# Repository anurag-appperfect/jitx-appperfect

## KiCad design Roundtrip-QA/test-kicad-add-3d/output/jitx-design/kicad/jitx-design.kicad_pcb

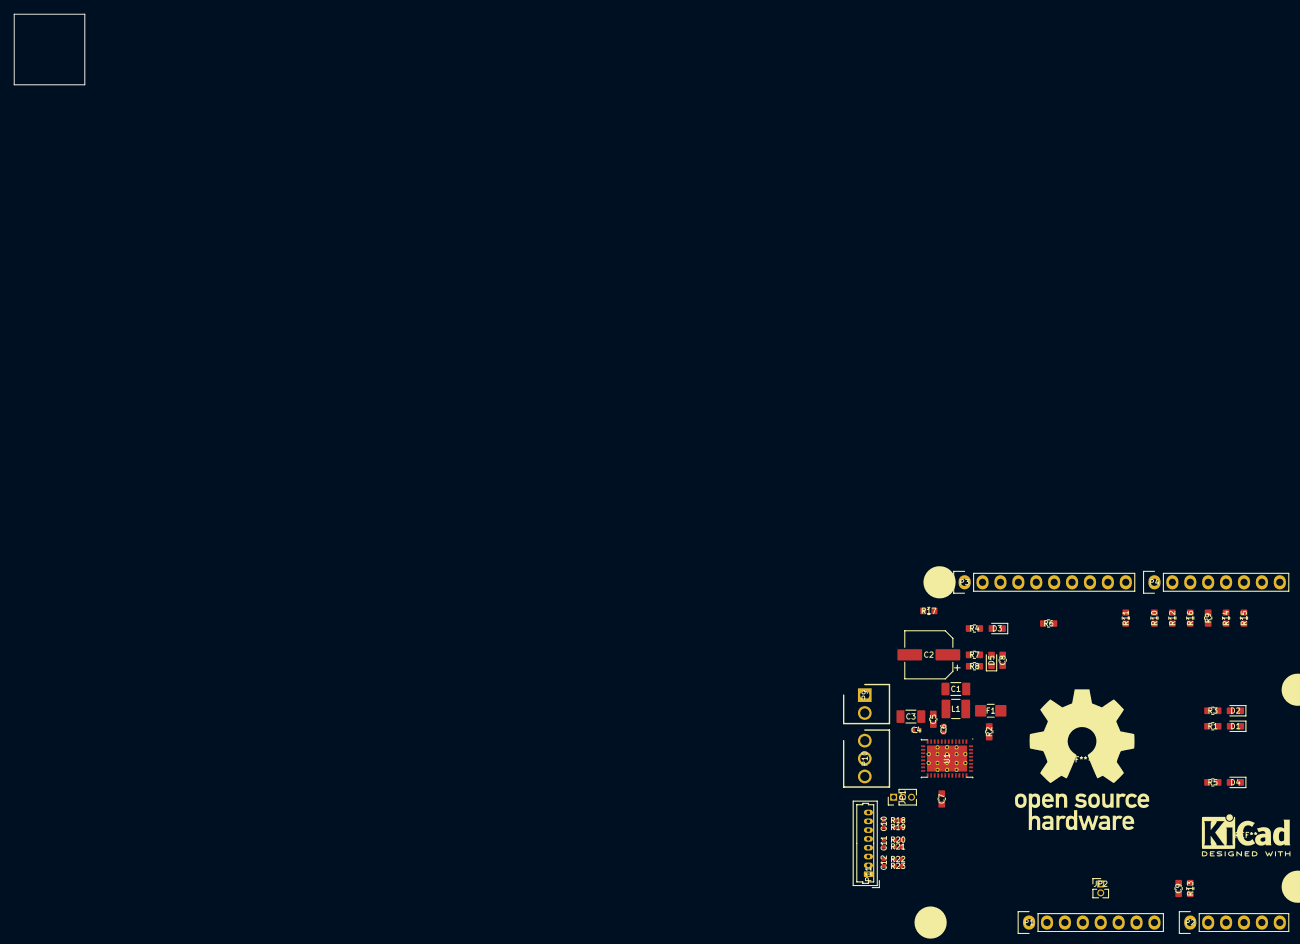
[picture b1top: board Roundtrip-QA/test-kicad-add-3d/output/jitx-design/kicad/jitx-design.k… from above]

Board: 4 copper layers, 57 parts (0 on the bottom side), 47 nets, no tracks yet.

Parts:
C1: c_1206_3216metric
C2: cp_elec_63x77
C3: c_1206_3216metric_1
C4, C6, C10, C11, C12: c_0402_1005metric
C5, C7, C8, C9: c_0603_1608metric
D1, D2, D3, D4: led_0603_1608metric
D5: d_0603_1608metric
F1: fuse_1206_3216metric_castellated
JP1: pinheader_1x03_p127mm_vertical
JP2: pinheader_1x02_p127mm_vertical
L1: l_1210_3225metric
P1: socket_strip_arduino_1x08
P2: socket_strip_arduino_1x06locked
P3: socket_strip_arduino_1x10locked
P4: socket_strip_arduino_1x08locked
P5, P6, P7, P8: arduino_1pinlocked
P9: Pkg_39773_0002
P10: Pkg_39773_0003
P11: molex_picoblade_53047_0810_1x08_p125mm_vertical
R1, R2, R3, R4, R5, R6, R7, R8, R9, R10, R11, R12, R13, R14, R15, R16, R17: r_0603_1608metric
R18, R19, R20, R21, R22, R23: r_0402_1005metric
SW1: kailh_pcb_socket_1u_cutout_pkg
U1: qfn_40_ep_5x7_pitch05mm

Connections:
A0: P2.1, R13.2
A1: C8.2, D5.2, P2.2, R7.1, R8.1
A4SDA: P2.5, P3.2
A5SCL: P2.6, P3.1
BRAKE: R10.2, U1.38
CS: R9.2, U1.36
DRVOFF: R16.2, U1.21
FAULT: D4.1, R15.2, U1.22
FB: C1.2, F1.2, L1.1, U1.3
FGOUT: R2.2, R12.2, U1.40
GND: C1.1, C7.2, C8.1, C9.1, D1.1, D2.1, D3.1, D5.1, P1.6, P1.7, P3.4, P11.1, R8.2, R17.2, R19.2, R21.2, R23.2, U1.2, U1.4, U1.41, U1.42, U1.43, U1.44, U1.45, U1.46, U1.47, U1.48, U1.49, U1.50, U1.51, U1.52, U1.53, U1.54, U1.55, U1.56, U1.57
GNDPWR: C2.2, C3.1, C4.1, P9.2, R17.1, U1.12, U1.15, U1.18
HAN: C10.1, P11.6, R19.1, U1.28
HAP: C10.2, P11.7, R18.1, U1.27
HBN: C11.1, P11.4, R21.1, U1.30
HBP: C11.2, P11.5, R20.1, U1.29
HCN: C12.1, P11.2, R23.1, U1.32
HCP: C12.2, P11.3, R22.1, U1.31
ILIM: C9.2, R13.1, U1.37
Net-C5-Pad1: C5.1, U1.8
Net-C6-Pad1: C6.1, U1.7
Net-C6-Pad2: C6.2, U1.6
Net-D1-Pad2: D1.2, R1.2
Net-D2-Pad2: D2.2, R3.2
Net-D3-Pad2: D3.2, R4.2
Net-D4-Pad2: D4.2, R5.2
Net-JP1-Pad2: JP1.2, P11.8
PWM: R11.2, U1.39
SLEEP: R14.2, U1.23
SW: L1.2, U1.5
U: P10.1, U1.13, U1.14
V: P10.2, U1.16, U1.17
VCC: F1.1, JP1.3, JP2.1, R3.1
W: P10.3, U1.19, U1.20
p2: P4.6, R15.1
p3**: P4.5, R14.1
p4: P4.4, R9.1
p5**: P4.3, R16.1
p6**: P4.2, R12.1
p7: P4.1, R10.1
p8: P3.10, R11.1
p11**MOSI: P3.7, U1.34
p12MISO: P3.6, R6.2, U1.33
p13SCK: P3.5, U1.35
p+3-3V: C7.1, JP1.1, P1.4, R1.1, R2.1, R5.1, R6.1, R18.2, R20.2, R22.2, U1.25
p+5V: JP2.2, P1.5
p+36V: C2.1, C3.2, C4.2, C5.2, P9.1, R4.1, R7.2, U1.9, U1.10, U1.11

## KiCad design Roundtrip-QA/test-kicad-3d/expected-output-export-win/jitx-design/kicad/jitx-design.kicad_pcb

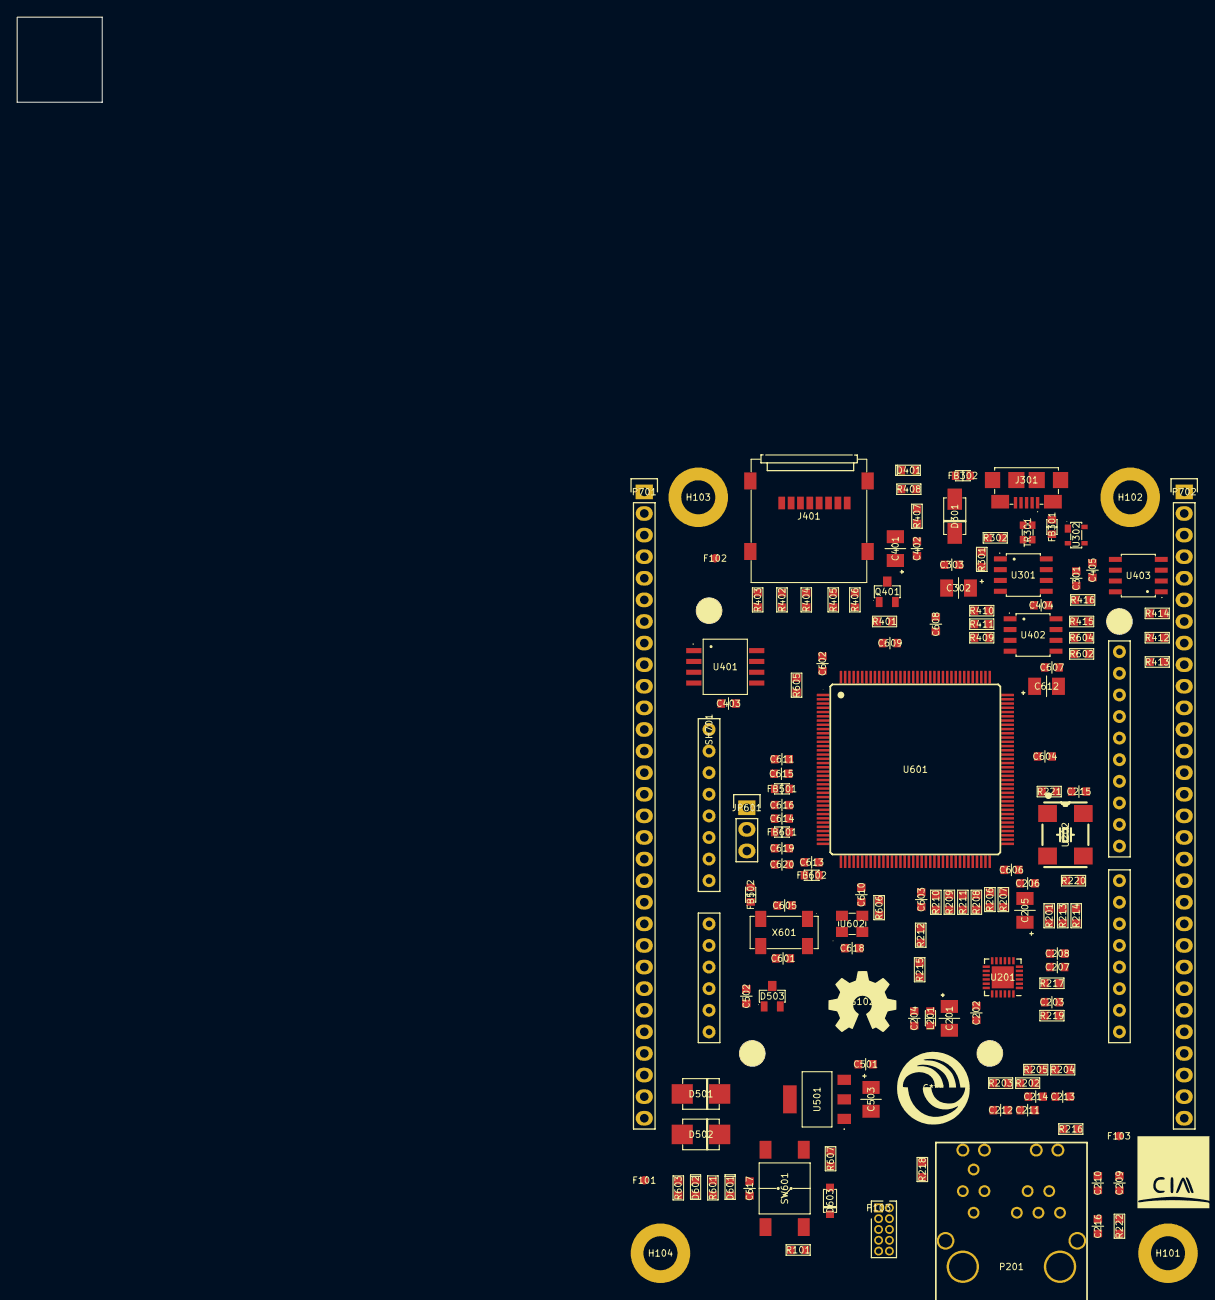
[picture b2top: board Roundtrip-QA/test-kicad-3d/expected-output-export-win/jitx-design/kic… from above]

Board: 4 copper layers, 141 parts (0 on the bottom side), 169 nets, no tracks yet.

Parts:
C201, C205: c_1206pol_1
C202, C203, C204, C206, C207, C208, C209, C210, C211, C212, C213, C214, C215: c_0603
C216, C301, C303, C402, C403, C404, C405, C501, C502, C601, C602, C603, C604, C605, C606, C607, C608, C609, C610, C611, C613, C614, C615, C616, C617, C618, C619, C620: c_0603_1
C302, C503, C612: c_1206pol_lp
C401: c_1206pol
D301: do_214ac_sma
D401, D601, D602: led_0603
D501, D502: do_214aa_smb
D503: sot_23
D603: sod_123
F101, F102, F103: fiducial_1mm_lp
FB301, FB302, FB501, FB502, FB601, FB602: fb_0603
G101: logo_ciaa_lp
G102: oshwa_lp
H101, H102, H103, H104: pcb_hole_lp
J301: usb_microab
J401: microsd_hinged
JP601: pin_header_straight_1x03
L201: fb_0603_1
P103: pin_header_straight_2x05_pitch127mm
P201: rj45_si_52003_f_poe_eth
P701, P702: pin_header_straight_1x30
Q401: sot_23_lp
R101, R222, R301, R302, R401, R402, R403, R404, R405, R406, R407, R408, R409, R410, R411, R412, R413, R414, R415, R416, R601, R602, R603, R604, R605, R606, R607: r_0603
R201, R202, R203, R204, R205, R206, R207, R208, R209, R210, R211, R212, R213, R214, R215, R216, R217, R218, R219, R220, R221: r_0603_1
SH701: arduino_as_uno_r3locked
SW601: tact_smd_4
TR301: srf2012
U201: qfn_24_1ep_4x4mm_pitch05mm
U202: oscillator_70x50mm
U301: soic_8
U302: sot_143_4
U401: soic_8_wide
U402, U403: soic_8_lp
U501: sot_223
U601: lqfp144
U602: si501_c
X601: Pkg_4soj

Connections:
BATPIN: D503.1, P701.20
CPUAIN0: P702.25, U601.77
CPUAIN1: P702.24, U601.78
CPUAIN2: P702.23, U601.79
CPUAIN3: P702.22, U601.80
CPUAUX-UART-CTSSPI-CLK: P701.12, U601.128
CPUAUX-UART-RTSSPI-CS: P701.13, U601.127
CPUAUX-UART-RXSPI-MISO: P701.10, U601.130
CPUAUX-UART-TXSPI-MOSIFTM3-CH2: P701.11, U601.129
CPUCAN-RD: P702.10, U601.98
CPUCAN-TD: P702.9, U601.97
CPUDAC-OUT: P701.18, U601.38
CPUDIN0: P702.13, U601.9
CPUDIN1: P702.14, U601.10
CPUDIN2: P701.23, U601.13
CPUDIN3: P701.24, U601.14
CPUDOUT0: P702.12, U601.95
CPUDOUT1: P702.21, U601.87
CPUDOUT2: P702.20, U601.88
CPUDOUT3: P702.11, U601.96
CPUDOUT4: P701.26, U601.120
CPUDOUT5: P701.27, U601.119
CPUDOUT6: P701.28, U601.118
CPUDOUT7: P701.29, U601.117
CPUEC-AI0: SH701.A0, U601.35
CPUEC-AI1: SH701.A1, U601.36
CPUEC-AI2: SH701.A2, U601.39
CPUEC-AI3: SH701.A3, U601.46
CPUEC-GPIO0: SH701.8, U601.76
CPUEC-GPIO1: SH701.7, U601.75
CPUEC-GPIO2: SH701.4, U601.85
CPUEC-I2C-SCL: SH701.A5-1, SH701.A5-2, U601.83
CPUEC-I2C-SDA: SH701.A4-1, SH701.A4-2, U601.84
CPUEC-PWM0: SH701.6, U601.60
CPUEC-PWM1: SH701.5, U601.61
CPUEC-PWM2: SH701.3, U601.62
CPUEC-PWM3: SH701.2, U601.63
CPUEC-PWM4: SH701.10, U601.54
CPUEC-PWM5: SH701.9, U601.15
CPUETH-CRS-DV: R211.1, U601.66
CPUETH-MDC: R214.1, U601.82
CPUETH-MDIO: R213.1, U601.81
CPUETH-REF-CLK: R220.2, U201.5, U601.72
CPUETH-RST: U201.15, U601.73
CPUETH-RXD0: R209.1, U601.65
CPUETH-RXD1: R210.1, U601.64
CPUETH-RXER: R212.2, U601.55
CPUETH-TXD0: R206.1, U601.68
CPUETH-TXD1: R207.1, U601.69
CPUETH-TXEN: R208.1, U601.67
CPUGPIO0: P701.9, U601.116
CPUGPIO1: P702.2, U601.99
CPUGPIO2: P701.8, U601.115
CPUGPIO3SPI2-SCK: SH701.13, U601.100
CPUGPIO4: P701.2, U601.114
CPUGPIO5SPI2-SOUT: SH701.11, U601.101
CPUGPIO6: P701.3, U601.113
CPUGPIO7SPI2-SIN: SH701.12, U601.102
CPUGPIO8: P701.4, U601.112
CPUGPIO9: P702.8, U601.103
CPUGPIO10: P702.4, U601.111
CPUGPIO11: P702.7, U601.104
CPUGPIO12: P702.5, U601.110
CPUGPIO13: P702.6, U601.105
CPUGPIO14: P702.3, U601.109
CPUGPIO15: P701.14, U601.106
CPUI2C-SCL: R604.2, U402.6, U403.6, U601.137
CPUI2C-SDA: R602.2, U402.5, U403.5, U601.138
CPUPGA1-DM: P701.22, U601.30
CPUPGA1-DP: P701.21, U601.29
CPUPTB5: P702.15, U601.86
CPURS232-CTS: P702.18, U601.90
CPURS232-RTS: P702.19, U601.89
CPURS232-RXD: P702.17, U601.91
CPURS232-TXD: P702.16, U601.92
CPURS485-DIR: P701.5, U601.131
CPURS485-RXD: P701.6, U601.133
CPURS485-TXD: P701.7, U601.136
CPUSD-CLK: J401.5, R605.2
CPUSD-CMD: J401.3, R404.2, U601.4
CPUSD-DAT0: J401.7, R405.2, U601.2
CPUSD-DAT1: J401.8, R406.2, U601.1
CPUSD-DAT2: J401.1, R403.2, U601.8
CPUSD-DAT3: J401.2, R402.1, U601.7
CPUSD-POW: Q401.1, R401.2, U601.126
CPUSPIFI-CLK: U401.6, U601.141
CPUSPIFI-CS: U401.1, U601.140
CPUSPIFI-HOLD: U401.7, U601.144
CPUSPIFI-MISO: U401.2, U601.143
CPUSPIFI-MOSI: U401.5, U601.142
CPUSPIFI-WP: U401.3, U601.139
CPUUSB-ID: D301.2, J301.4, U601.123
CPUUSBD-N: TR301.3, U302.2, U601.20
CPUUSBD-P: TR301.2, U302.3, U601.19
CPUVREFL: C613.2, C614.2, C616.1, FB602.1, U601.33
EthernetLED-100M: P201.15, R217.2, U201.2
EthernetLED-LINK: P201.12, U201.3
EthernetRX-N: C214.1, P201.5, R205.2, U201.22
EthernetRX-P: C213.1, P201.4, R204.2, U201.23
EthernetTX-N: C212.1, P201.3, R203.2, U201.20
EthernetTX-P: C211.1, P201.1, R202.2, U201.21
GND: C201.2, C202.2, C203.2, C204.2, C205.2, C206.2, C207.2, C208.2, C209.2, C210.2, C211.2, C212.2, C213.2, C214.2, C215.2, C216.2, C301.2, C302.2, C303.2, C401.2, C402.2, C403.2, C404.2, C405.2, C501.2, C502.2, C503.2, C601.2, C602.2, C603.2, C604.2, C605.2, C606.2, C607.2, C608.2, C609.2, C610.2, C611.2, C612.2, C615.2, C617.1, C618.2, D401.2, D601.2, D602.2, FB302.1, FB502.1, J301.5, J401.6, J401.9, J401.10, J401.11, J401.12, P103.3, P103.5, P701.30, P702.1, R218.1, R219.2, R222.2, R301.1, R402.2, R407.2, R410.2, R411.2, R413.2, R414.2, R415.2, R416.2, SH701.GND1, SH701.GND2, SH701.GND3, SW601.2, U201.25, U201.26, U201.27, U201.GND, U202.2, U301.3, U401.4, U402.4, U403.4, U501.1, U601.6, U601.17, U601.18, U601.44, U601.57, U601.71, U601.93, U601.107, U601.121, U601.134, U602.2, X601.2, X601.4
GNDA: C619.2, C620.1, FB502.2, FB602.2, U601.34
GNDPWR: C216.1, H101.1, H102.1, H103.1, H104.1, P201.6, P201.7, P201.16, P201.17, R222.1
IOArefA: C614.1, C616.2, FB601.1, JP601.3, SH701.AREF, U601.32
Net-C207-Pad1: C207.1, C208.1, U201.6
Net-C401-Pad1: C401.1, C402.1, J401.4, Q401.3, R403.1, R404.1, R405.1, R406.1, R407.1, R408.1
Net-C601-Pad1: C601.1, U601.41, X601.3
Net-C605-Pad1: C605.1, U601.40, X601.1
Net-C613-Pad1: C613.1, U601.37
Net-C615-Pad1: C615.1, U601.21
Net-C617-Pad2: C617.2, D603.1, R607.2, SW601.1, U601.74
Net-C619-Pad1: C619.1, C620.2, FB601.2, JP601.2
Net-D401-Pad1: D401.1, R408.2
Net-D601-Pad1: D601.1, R601.1
Net-D602-Pad1: D602.1, R603.1
Net-FB301-Pad2: FB301.2, J301.1
Net-P103-Pad9: P103.9, R101.2
Net-P201-Pad13: P201.13, R218.2
Net-P201-Pad14: P201.14, R216.1
Net-R201-Pad2: R201.2, R213.2, U201.12
Net-R206-Pad2: R206.2, U201.17
Net-R207-Pad2: R207.2, U201.18
Net-R208-Pad2: R208.2, U201.16
Net-R209-Pad2: R209.2, U201.8
Net-R210-Pad2: R210.2, U201.7
Net-R211-Pad2: R211.2, U201.11
Net-R212-Pad1: R212.1, U201.10
Net-R214-Pad2: R214.2, U201.13
Net-R215-Pad2: R215.2, U201.14
Net-R219-Pad1: R219.1, U201.24
Net-R220-Pad1: R220.1, U202.3
Net-R221-Pad1: R221.1, U202.1
Net-R409-Pad1: R409.1, U402.3
Net-R410-Pad1: R410.1, U402.1
Net-R411-Pad1: R411.1, U402.2
Net-R412-Pad2: R412.2, U403.1
Net-R413-Pad1: R413.1, U403.2
Net-R414-Pad1: R414.1, U403.3
Net-R415-Pad1: R415.1, U402.7
Net-R416-Pad1: R416.1, U403.7
Net-R601-Pad2: R601.2, U601.58
Net-R603-Pad2: R603.2, U601.59
Net-R605-Pad1: R605.1, U601.3
Net-R606-Pad1: R606.1, U601.45
Net-R606-Pad2: R606.2, U602.3
PoE-MA-+: P201.8, P702.29
PoE-MA--: P201.9, P702.30
PoE-MB-+: P201.10, P702.27
PoE-MB--: P201.11, P702.28
RESET: D603.2, P103.10, P701.17, SH701.RST
TCK: P103.4, U601.50
TDIEC-UART-RX: P103.8, SH701.0, U601.51
TDOEC-UART-TX: P103.6, SH701.1, U601.52
TMS: P103.2, U601.53
USB-JTAG-UART-RXD: P103.7, P701.16, U601.12
USB-JTAG-UART-TXD: P701.15, R101.1, U601.11
USB-VBUS: C302.1, C303.1, D502.1, FB301.1, U301.6, U301.8, U302.4, U601.22
USBOTGCHS-OTG: D301.1, FB302.2, J301.6, J301.7, J301.8, J301.9, J301.10, J301.11, U302.1
USBOTGUSB0-PPWR: R301.2, U301.1, U601.125
USBOTGUSB0-PWR-FAULT: R302.2, U301.2, U601.124
USBOTGUSB-D-OTG-N: J301.2, TR301.4
USBOTGUSB-D-OTG-P: J301.3, TR301.1
VBAT: C502.1, D503.3, U601.42
VDD-ETH: C201.1, C202.1, C203.1, C209.1, C210.1, L201.2, P201.2, R202.1, R203.1, R204.1, R205.1, R217.1, U201.1, U201.19
p5VPIN: D501.1, P701.19
p+3-3V: C204.1, C205.1, C206.1, C215.1, C403.1, C404.1, C405.1, C503.1, C602.1, C603.1, C604.1, C606.1, C607.1, C608.1, C609.1, C610.1, C611.1, C612.1, C618.1, D503.2, FB501.1, L201.1, P103.1, Q401.2, R201.1, R215.1, R216.2, R221.2, R302.1, R401.1, R409.2, R412.1, R602.1, R604.1, R607.1, SH701.IREF, SH701.p3V3, U201.9, U202.4, U401.8, U402.8, U403.8, U501.2, U501.4, U601.5, U601.16, U601.43, U601.56, U601.70, U601.94, U601.108, U601.122, U601.135, U602.1, U602.4
p+3-3VADC: FB501.2, JP601.1, U601.31
p+5V: C301.1, C501.1, D501.2, D502.2, P701.1, P701.25, P702.26, SH701.p5V, U301.7, U501.3

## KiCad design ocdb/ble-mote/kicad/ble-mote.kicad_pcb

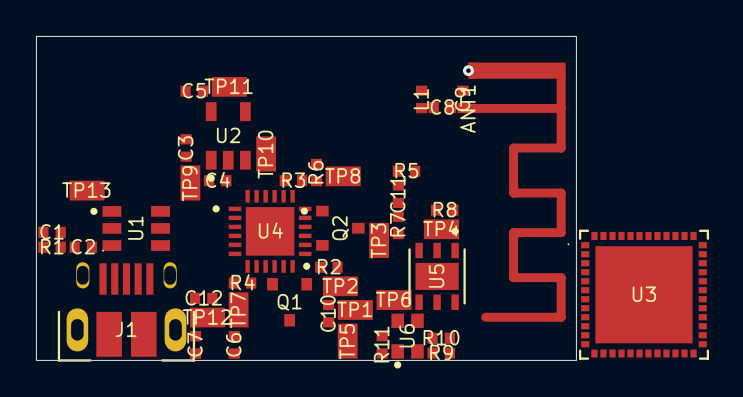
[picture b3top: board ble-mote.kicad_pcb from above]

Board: 4 copper layers, 30.0 x 18.0 mm, 48 parts (1 on the bottom side), 30 nets.

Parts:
ANT1: ant_2GHz4_inverted_f_geom
C1, C2, C3, C4, C5, C6, C7, C8, C9, C10, C11, C12: ipc_two_pin_landpattern
J1: amphenol_10103594_0001lf
J2: amphenol_minitek127_pkg
L1: ipc_two_pin_landpattern
Q1, Q2: SOT95P280X100_3N
R1, R2, R3, R4, R5, R6, R7, R8, R9, R10, R11: ipc_two_pin_landpattern
TP1, TP2, TP3, TP4, TP5, TP6, TP7, TP8, TP9, TP10, TP11, TP12, TP13: rc_landpattern
U1: SOT95P280X145_6N
U2: SOT95P280X145_5N
U3: pqfn50p700x700x104_49n
U4: qfn_landpattern
U5: son100p300x300x80_7n
U6: rgb_2020

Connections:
D+: J1.3, U1.5, U4.3
D-: J1.2, U1.6, U4.4
DTR_ECI: Q2.2, R2.1, U4.15
EN: Q1.3, TP5.p, U3.9
ESP-RX: TP2.p, U3.40, U4.13
ESP-TX: TP1.p, U3.41, U4.12
H-I2C_scl: R8.1, TP4.p, U3.36, U5.6
H-I2C_sda: R7.1, TP3.p, U3.39, U5.1
LNA-IN: C8.1, L1.2, U3.2
P3V3: C5.2, C6.2, C7.2, C10.2, C11.2, C12.2, R4.2, R5.1, R6.1, R7.2, R8.2, TP10.p, U2.5, U3.1, U3.3, U3.4, U3.19, U3.37, U3.43, U3.46, U4.5, U4.6, U4.7, U5.5, U6.3
P5V0: C3.1, C4.2, J2.1, J2.2, TP9.p, U1.4, U2.1, U2.3, U4.8
PC-RESET: J2.6, R6.2, U3.42
PC-RX: J2.8, TP8.p, U3.10
PC-SET: J2.9, R5.2, U3.38
PC-TX: J2.10, TP7.p, U3.11
RTS_ECI: Q1.2, R3.1, U4.11
VBUS: C2.1, J1.1, U1.1, U1.3
b: Q1.1, R2.2
c: Q2.3, TP6.p, U3.23
g: R10.2, U6.4
gnd: ANT1.gnd, C1.2, C2.2, C3.2, C4.1, C5.1, C6.1, C7.1, C9.1, C10.1, C11.1, C12.1, J1.5, J2.3, J2.4, L1.1, R1.2, TP11.p, TP12.p, TP13.p, U1.2, U2.2, U3.49, U4.2, U4.25, U5.2
l_b: R11.2, U6.2
launch: ANT1.launch, C8.2, C9.2
nRST: R4.1, U4.9
proc_q1_b: Q2.1, R3.2
pwm0_timer: R9.1, U3.16
pwm1_timer: R10.1, U3.15
pwm2_timer: R11.1, U3.14
r: R9.2, U6.1
rid_p1: C1.1, J1.6, J1.7, J1.8, J1.9, J1.10, J1.11, J1.13, J1.14, R1.1

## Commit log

2022-02-25 Update Jenkinsfile
2022-02-25 Update Dockerfile
2022-03-01 updated Jenkinsfile
2022-03-02 Updating Jenkinsfile
2022-03-03 Updating Dockerfile and Jenkisfile
2022-03-03 Updating the Jenkinsfile
2022-03-09 Updating Dockerfile and Jenkinsfile
2022-03-10 Adding provison and updating file
2022-03-10 Adding .env and updating Jenkinsfile
2022-03-14 Adding dockerfile for ubuntu-bionic and ubuntu-xenial
2022-03-14 Adding docker file for Centos 7
2022-03-14 Updating Jenkinsfile and dockerfiles
2022-03-14 Updating Jenkins file
2022-03-14 Updating the dockerfile
